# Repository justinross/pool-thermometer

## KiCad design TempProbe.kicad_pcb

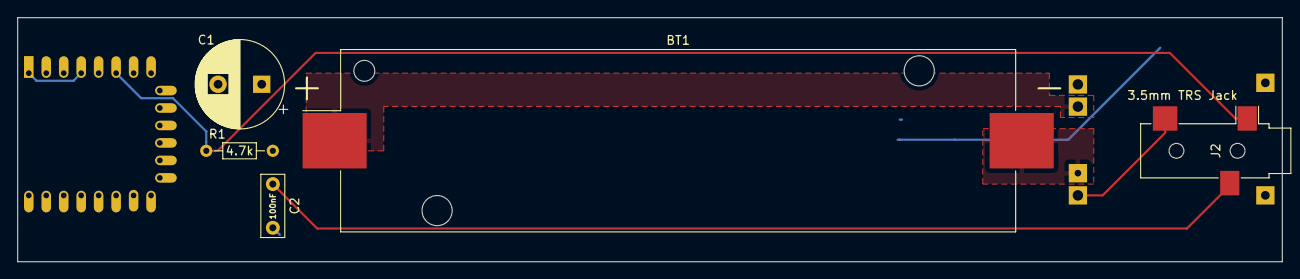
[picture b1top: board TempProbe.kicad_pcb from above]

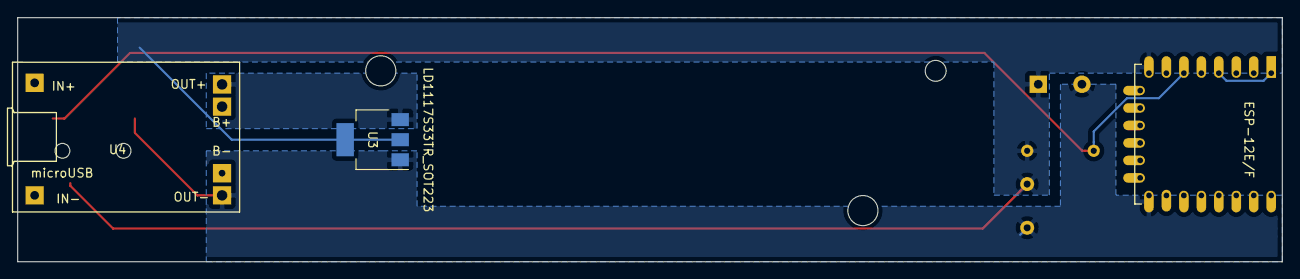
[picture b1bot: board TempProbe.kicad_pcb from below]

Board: 2 copper layers, 144.8 x 27.9 mm, 8 parts (3 on the bottom side), 7 nets.

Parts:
BT1: 3.7v 18650 Cell; BatteryHolder_Keystone_1042_1x18650
C1: 1000uF; CP_Radial_D10.0mm_P5.00mm
C2: 100nF; C_Disc_D7.0mm_W2.5mm_P5.00mm
ESP-12E/F: ESP-12F; ESP-12E
J2: 3.5mm TRS Jack; Jack_3.5mm_CUI_SJ-3523-SMT_Horizontal
R1: 4.7k; R_Axial_DIN0204_L3.6mm_D1.6mm_P7.62mm_Horizontal
U3: LD1117S33TR_SOT223; SOT-223-3_TabPin2
U4: TP4056 Charging Module; 4056E_LiIon_loader_prot

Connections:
unnamed: BT1.1, U4.3
unnamed: BT1.2, U4.4
unnamed: C1.1, C2.1, ESP-12E/F.8, J2.R, R1.2, U3.2
unnamed: C1.2, C2.2, ESP-12E/F.9, J2.T, U3.1, U4.6
unnamed: ESP-12E/F.6, J2.S, R1.1
unnamed: ESP-12E/F.1, ESP-12E/F.4
unnamed: U3.3, U4.5
